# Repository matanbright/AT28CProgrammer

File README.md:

# AT28C Programmer

Programmer for AT28C64 and AT28C256 EEPROMs.

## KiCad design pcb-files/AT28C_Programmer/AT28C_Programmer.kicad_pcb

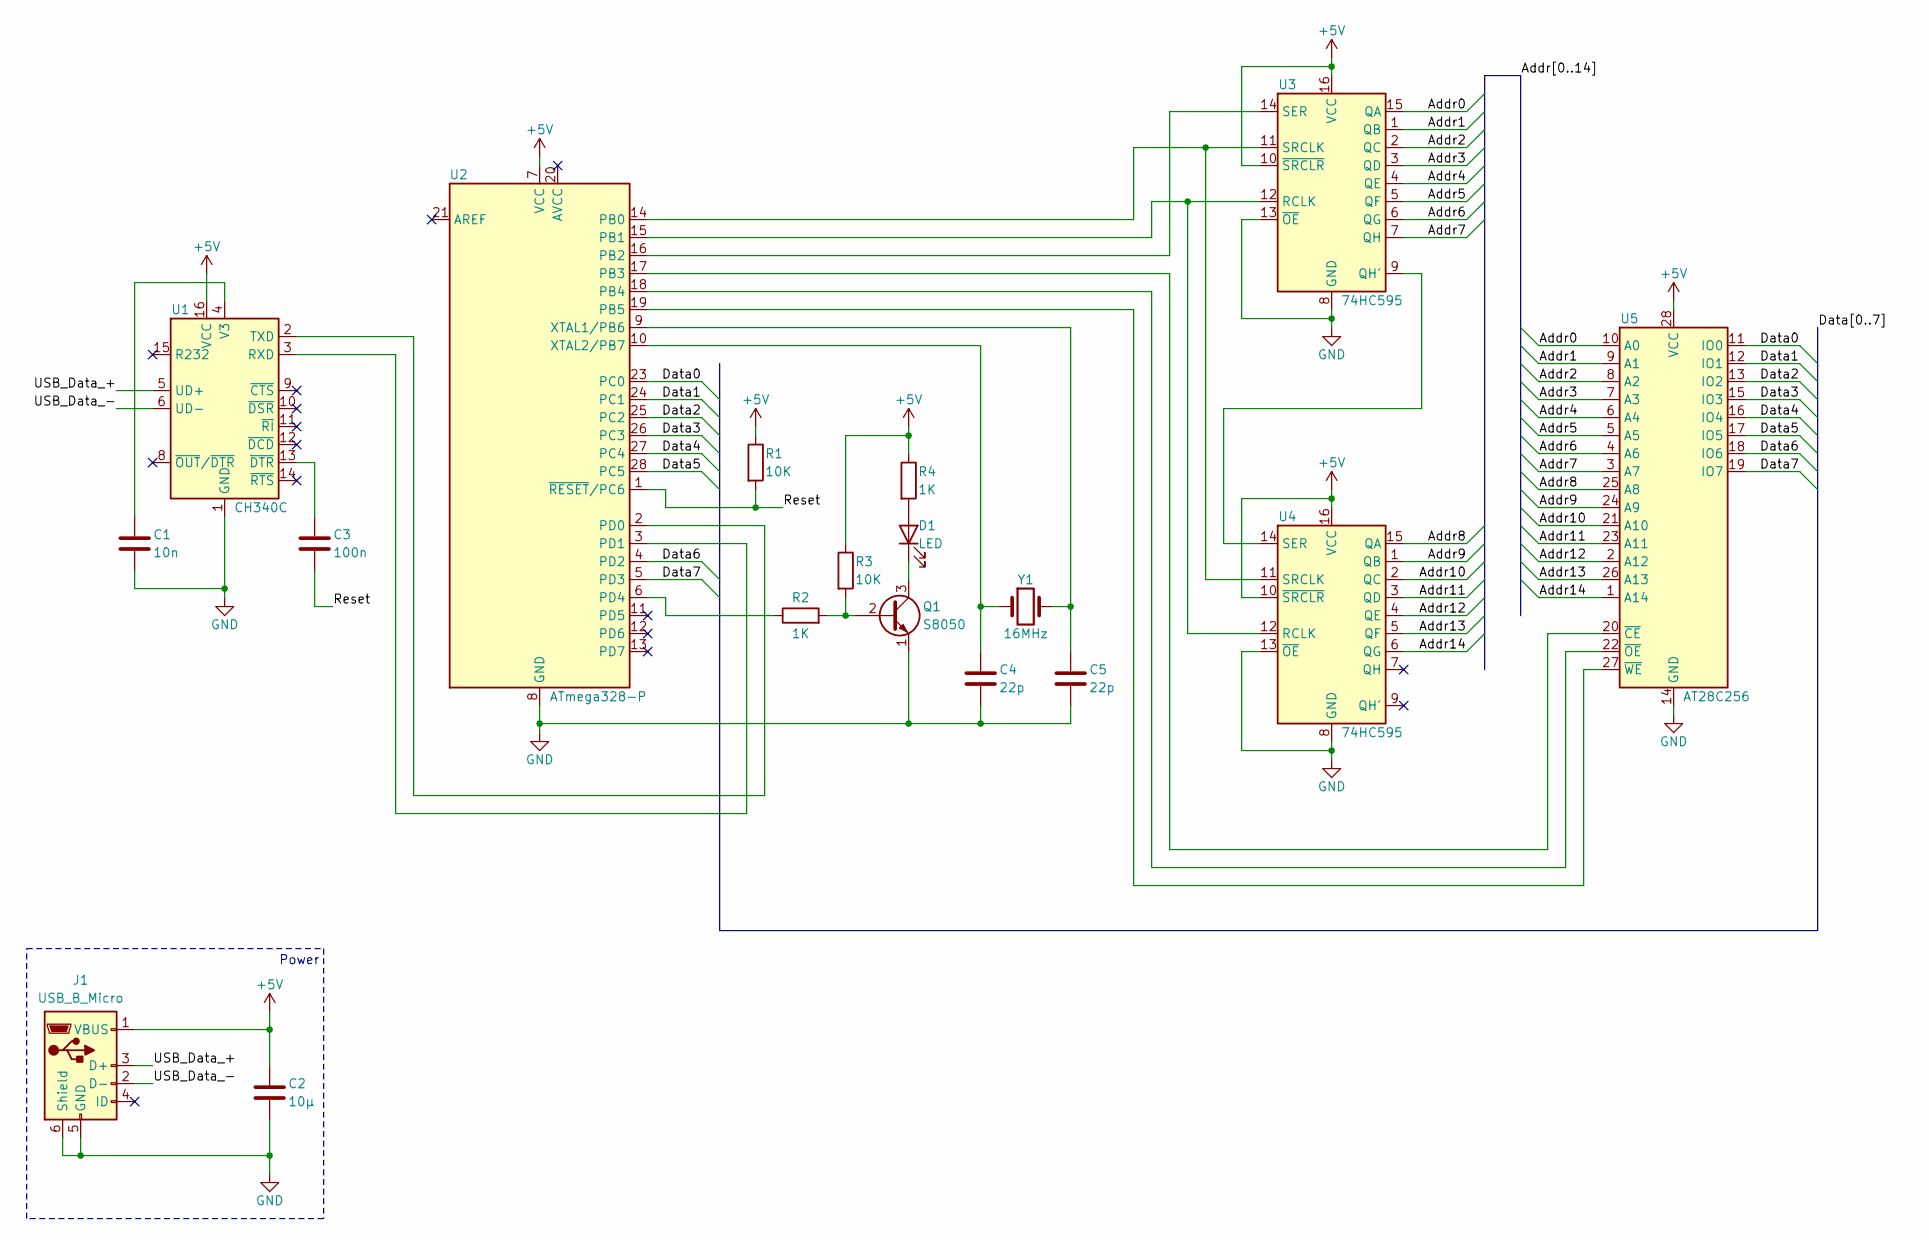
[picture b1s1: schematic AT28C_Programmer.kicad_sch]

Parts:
C1: 10n; C_Disc_D5.1mm_W3.2mm_P5.00mm
C2: 10μ; C_Radial_D4.0mm_H7.0mm_P1.50mm
C3: 100n; C_Disc_D5.1mm_W3.2mm_P5.00mm
C4, C5: 22p; C_Disc_D5.1mm_W3.2mm_P5.00mm
D1: LED; LED_D3.0mm
J1: USB_B_Micro; USB_Micro-B_Amphenol_10103594-0001LF_Horizontal
Q1: S8050; TO-92_Inline
R1, R3: 10K; R_Axial_DIN0207_L6.3mm_D2.5mm_P7.62mm_Horizontal
R2, R4: 1K; R_Axial_DIN0207_L6.3mm_D2.5mm_P7.62mm_Horizontal
U1: CH340C; SOIC-16_3.9x9.9mm_P1.27mm
U2: ATmega328-P; DIP-28_W7.62mm
U3, U4: 74HC595; DIP-16_W7.62mm
U5: AT28C256; DIP_Socket-28_W11.9_W12.7_W15.24_W17.78_W18.5_3M_228-1277-0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
Y1: 16MHz; Crystal_HC49-4H_Vertical

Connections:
+5V: C2.1, J1.1 (VBUS), R1.1, R3.1, R4.1, U1.16 (VCC), U2.7 (VCC), U3.10 (~SRCLR), U3.16 (VCC), U4.10 (~SRCLR), U4.16 (VCC), U5.28 (VCC)
/Addr0: U3.15 (QA), U5.10 (A0)
/Addr1: U3.1 (QB), U5.9 (A1)
/Addr2: U3.2 (QC), U5.8 (A2)
/Addr3: U3.3 (QD), U5.7 (A3)
/Addr4: U3.4 (QE), U5.6 (A4)
/Addr5: U3.5 (QF), U5.5 (A5)
/Addr6: U3.6 (QG), U5.4 (A6)
/Addr7: U3.7 (QH), U5.3 (A7)
/Addr8: U4.15 (QA), U5.25 (A8)
/Addr9: U4.1 (QB), U5.24 (A9)
/Addr10: U4.2 (QC), U5.21 (A10)
/Addr11: U4.3 (QD), U5.23 (A11)
/Addr12: U4.4 (QE), U5.2 (A12)
/Addr13: U4.5 (QF), U5.26 (A13)
/Addr14: U4.6 (QG), U5.1 (A14)
/Data0: U2.23 (PC0), U5.11 (IO0)
/Data1: U2.24 (PC1), U5.12 (IO1)
/Data2: U2.25 (PC2), U5.13 (IO2)
/Data3: U2.26 (PC3), U5.15 (IO3)
/Data4: U2.27 (PC4), U5.16 (IO4)
/Data5: U2.28 (PC5), U5.17 (IO5)
/Data6: U2.4 (PD2), U5.18 (IO6)
/Data7: U2.5 (PD3), U5.19 (IO7)
/Reset: C3.2, R1.2, U2.1 (~RESET/PC6)
/USB_Data_+: J1.3 (D+), U1.5 (UD+)
/USB_Data_-: J1.2 (D-), U1.6 (UD-)
GND: C1.2, C2.2, C4.2, C5.2, J1.5 (GND), J1.6 (Shield), Q1.1 (E), U1.1 (GND), U2.8 (GND), U2.22 (GND), U3.8 (GND), U3.13 (~OE), U4.8 (GND), U4.13 (~OE), U5.14 (GND)
unnamed: D1.2 (A), R4.2
unnamed: D1.1 (K), Q1.3 (C)
unnamed: Q1.2 (B), R2.2, R3.2
unnamed: U1.3 (RXD), U2.3 (PD1)
unnamed: U1.2 (TXD), U2.2 (PD0)
unnamed: C1.1, U1.4 (V3)
unnamed: C3.1, U1.13 (~DTR)
unnamed: U2.14 (PB0), U3.11 (SRCLK), U4.11 (SRCLK)
unnamed: U2.15 (PB1), U3.12 (RCLK), U4.12 (RCLK)
unnamed: U2.16 (PB2), U3.14 (SER)
unnamed: U2.17 (PB3), U5.20 (~CE)
unnamed: U2.18 (PB4), U5.22 (~OE)
unnamed: U2.19 (PB5), U5.27 (~WE)
unnamed: R2.1, U2.6 (PD4)
unnamed: C5.1, U2.9 (XTAL1/PB6), Y1.2
unnamed: C4.1, U2.10 (XTAL2/PB7), Y1.1
unnamed: U3.9 (QH'), U4.14 (SER)

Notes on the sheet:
Power

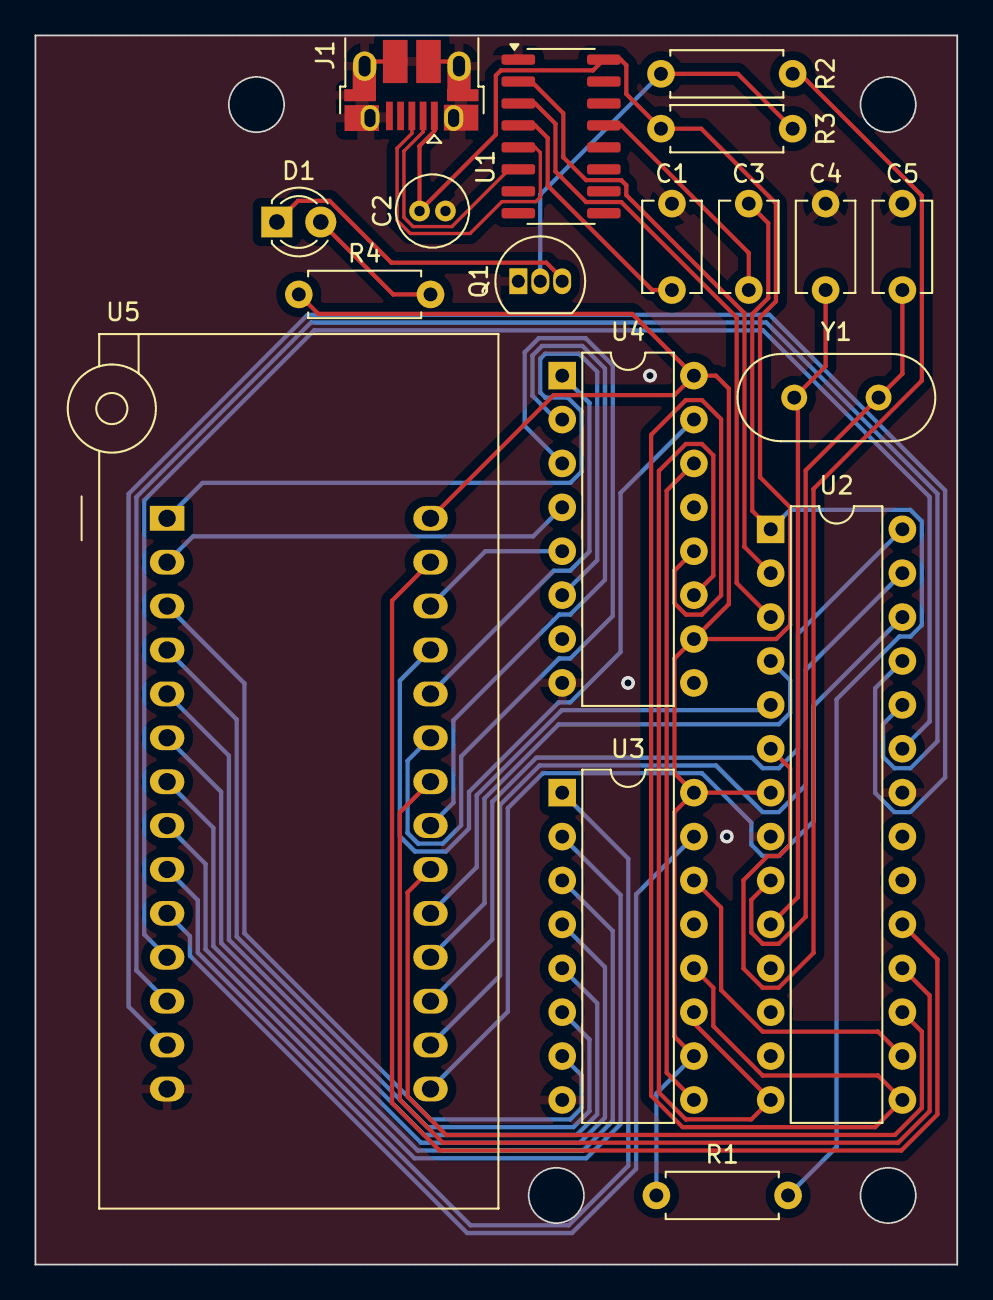
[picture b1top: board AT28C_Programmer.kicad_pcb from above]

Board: 2 copper layers, 53.3 x 71.1 mm, 18 parts (0 on the bottom side), 45 nets.
